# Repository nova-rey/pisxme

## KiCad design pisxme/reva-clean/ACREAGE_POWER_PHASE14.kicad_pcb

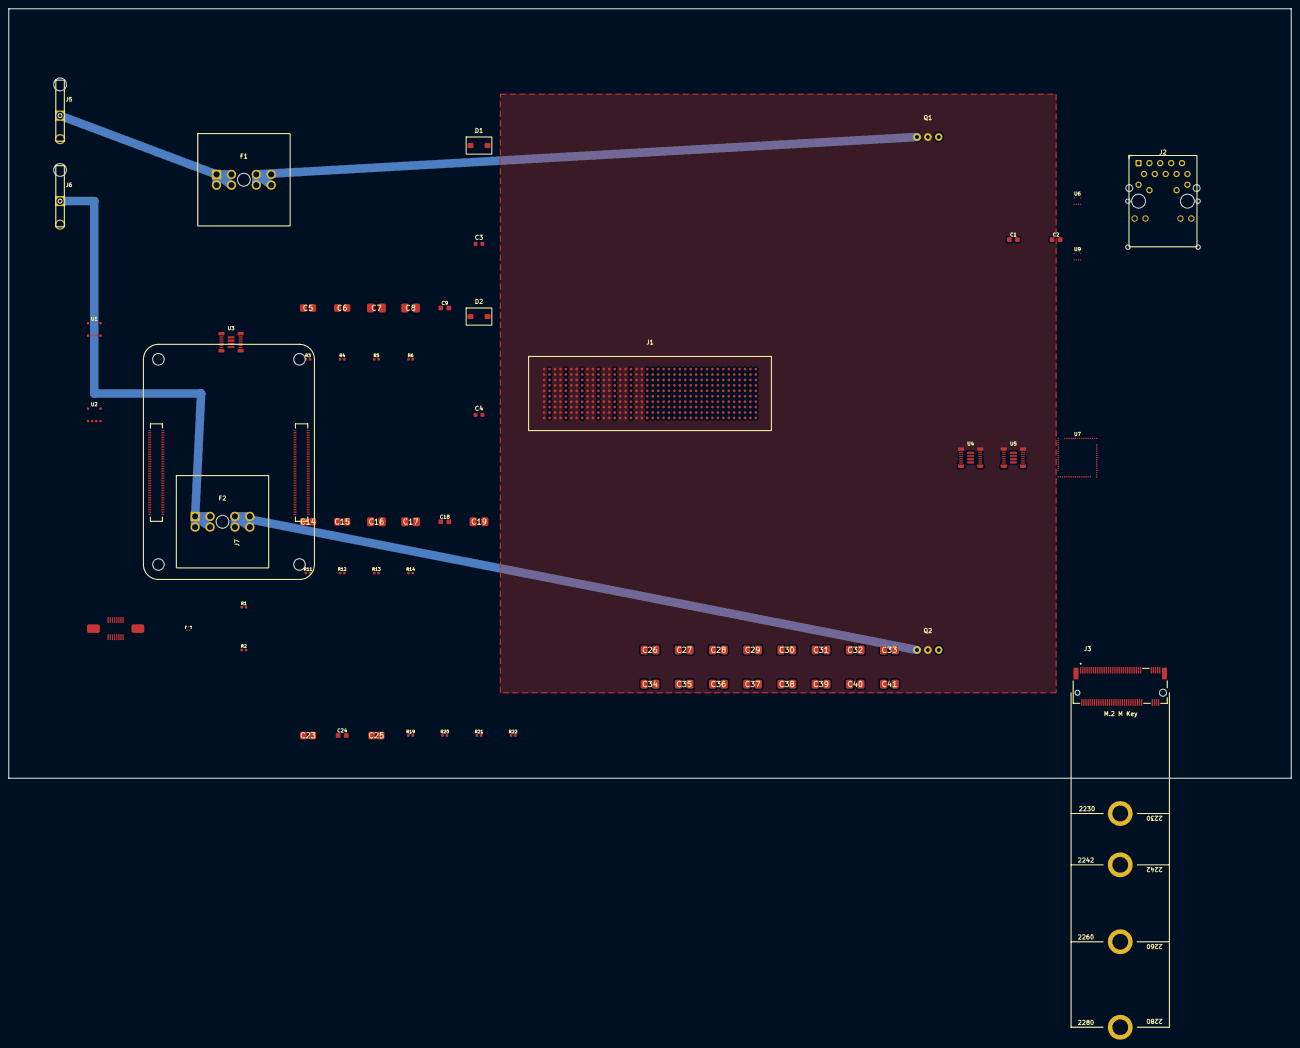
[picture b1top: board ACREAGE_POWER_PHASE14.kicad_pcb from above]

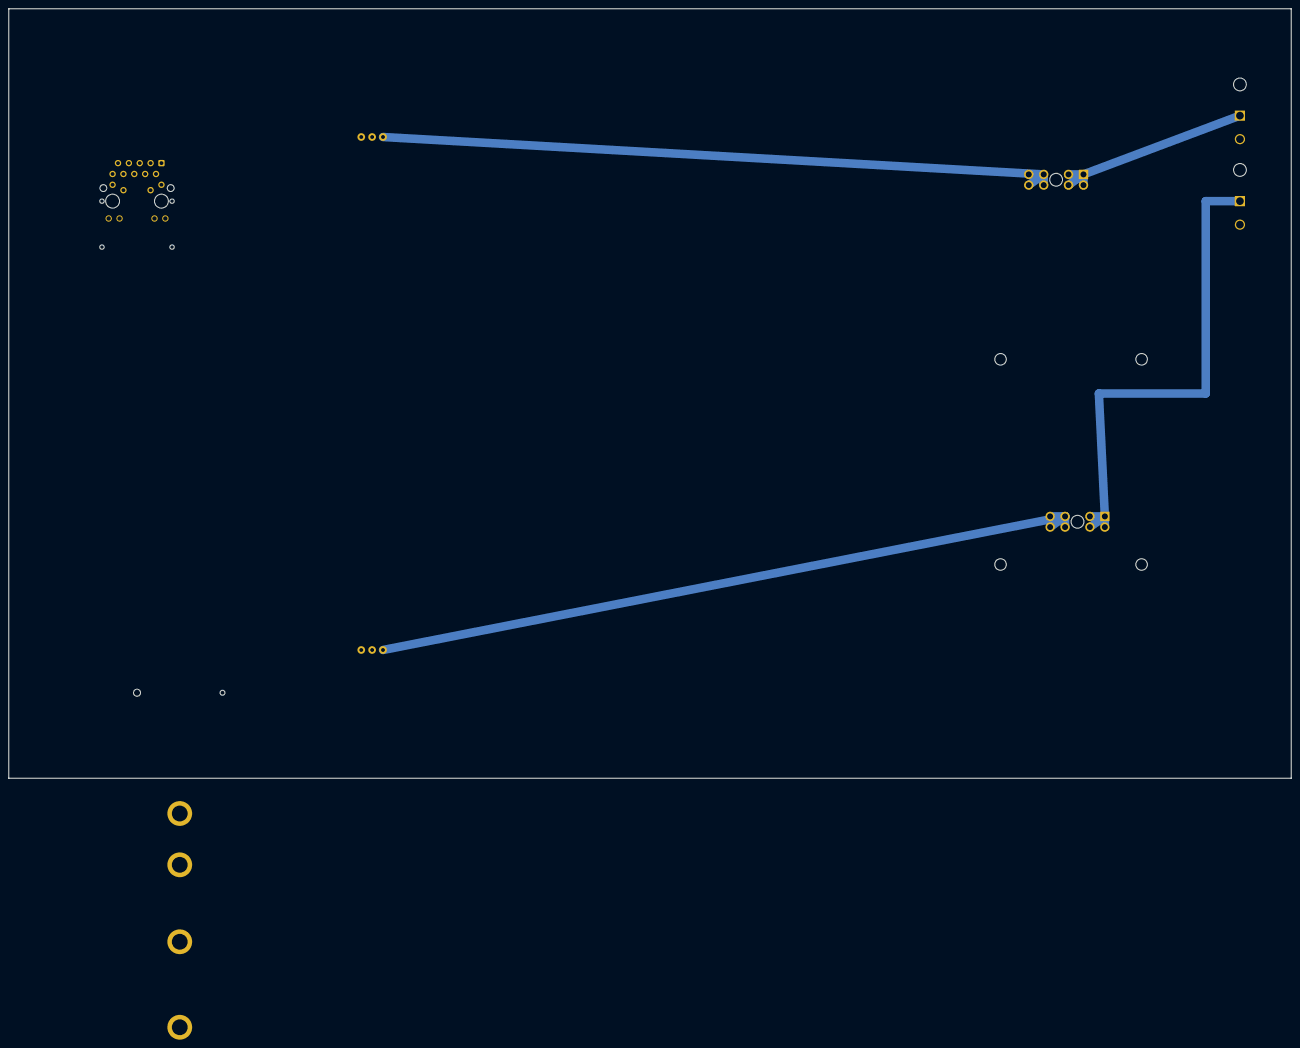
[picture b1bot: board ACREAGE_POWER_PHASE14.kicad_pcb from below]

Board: 6 copper layers, 300.0 x 180.0 mm, 72 parts (2 on the bottom side), 48 nets.

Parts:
C1, C2, C9, C18, C24: C_0805_2012Metric
C3, C4: C_0603_1608Metric
C5, C6, C14, C15, C23, C25: C_1206_3216Metric
C7, C8, C16, C17, C19, C26, C27, C28, C29, C30, C31, C32, C33, C34, C35, C36, C37, C38, C39, C40, C41: C_1210_3225Metric
D1, D2: SMBJ18A; TVS_SMBJ18A_DO214AA
F1, F2: 178.6165.0001; ATO_FuseHolder_17861650001
J1: 74221-101LF; PiSXMeRevAClean_SXM2_74221_101LF
J2: A70-112-331N126; EDAC_A70_112_331N126
J3: JAE SM3ZS067U410ABR1000 B-key SATA socket; JAE_SM3ZS067U410ABR1000_BKEY
J4: Amphenol 10171746-00021LF USB-C USB2 SERVICE; USB_C_SERVICE_10171746
J5, J6: 0039300020; Molex_0039300020_5569_2P_RA
J7: Raspberry-Pi-5-Compute-Module; PiSXMeRevAClean_Raspberry_Pi_5_Compute_Module
MECH_M2_2280: JAE SM3ZS067U410ABR1000 / 2280 card envelope; M2_2280_RETENTION_ENVELOPE
MECH_V100: REV_A_EMPIRICAL_RISK: 150x95mm cooler/backplate e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; V100_COOLER_BACKPLATE_ENVELOPE
Q1, Q2: CSD19536KCS; CSD19536KCS_TO220
R1, R2, R3, R4, R5, R6, R11, R12, R13, R14, R19, R20, R21, R22: R_0402_1005Metric
U1, U2: LM74700QDBVRQ1; LM74700QDBVRQ1_SOT23_6
U3, U4, U5: TPSM63606RDLR; TPSM63606RDLR_RDL0020
U6, U9: TPD4E004DRYR; TPD4E004DRYR_WSON6
U7: TUSB9261IPVP; TUSB9261IPVP_HTQFP64
U8: Texas_DRT_3

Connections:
12V_PROTECTED: C5.1, C6.1, C14.1, C15.1, C23.1, C24.1, C25.1, J1.A22, J1.A23, J1.A25, J1.A26, J1.A28, J1.A29, J1.A31, J1.A32, J1.A34, J1.A35, J1.A37, J1.A38, J1.A40, J1.B22, J1.B23, J1.B25, J1.B26, J1.B28, J1.B29, J1.B31, J1.B32, J1.B34, J1.B35, J1.B37, J1.B38, J1.B40, J1.C22, J1.C23, J1.C25, J1.C26, J1.C28, J1.C29, J1.C31, J1.C32, J1.C34, J1.C35, J1.C37, J1.C38, J1.C40, J1.D22, J1.D23, J1.D25, J1.D26, J1.D28, J1.D29, J1.D31, J1.D32, J1.D34, J1.D35, J1.D37, J1.D38, J1.D40, J1.E22, J1.E23, J1.E25, J1.E26, J1.E28, J1.E29, J1.E31, J1.E32, J1.E34, J1.E35, J1.E37, J1.E38, J1.E40, J1.F22, J1.F23, J1.F25, J1.F26, J1.F28, J1.F29, J1.F31, J1.F32, J1.F34, J1.F35, J1.F37, J1.F38, J1.F40, J1.G22, J1.G23, J1.G25, J1.G26, J1.G28, J1.G29, J1.G31, J1.G32, J1.G34, J1.G35, J1.G37, J1.G38, J1.G40, J1.H22, J1.H23, J1.H25, J1.H26, J1.H28, J1.H29, J1.H31, J1.H32, J1.H34, J1.H35, J1.H37, J1.H38, J1.H40, J1.J22, J1.J23, J1.J25, J1.J26, J1.J28, J1.J29, J1.J31, J1.J32, J1.J34, J1.J35, J1.J37, J1.J38, J1.J40, J1.K22, J1.K23, J1.K25, J1.K26, J1.K28, J1.K29, J1.K31, J1.K32, J1.K34, J1.K35, J1.K37, J1.K38, J1.K40, Q1.2, Q2.2, U1.4, U2.4, U3.1, U3.5, U3.14, U3.16, U4.1, U4.5, U4.14, U4.16, U5.1, U5.5, U5.14, U5.16
/CORE_CM5/CM5_5V: J7.77, J7.79, J7.81, J7.83, J7.85, J7.87
/CORE_CM5/CM5_PER0_N: J1.A3, J7.118
/CORE_CM5/CM5_PER0_P: J1.A2, J7.116
/CORE_CM5/CM5_PERST: J1.E18, J7.109
/CORE_CM5/CM5_PET0_N: C2.1, J7.124
/CORE_CM5/CM5_PET0_P: C1.1, J7.122
/CORE_CM5/CM5_REFCLK_N: J1.F7, J7.112
/CORE_CM5/CM5_REFCLK_P: J1.E7, J7.110
/CORE_CM5/POWER_GND: J7.1, J7.2, J7.7, J7.8, J7.13, J7.14, J7.22, J7.23, J7.32, J7.33, J7.42, J7.43, J7.52, J7.53, J7.59, J7.60, J7.65, J7.66, J7.71, J7.74, J7.98, J7.107, J7.108, J7.113, J7.114, J7.119, J7.120, J7.125, J7.126, J7.131, J7.132, J7.137, J7.138, J7.144, J7.150, J7.155, J7.156, J7.161, J7.162, J7.167, J7.168, J7.173, J7.174, J7.179, J7.180, J7.185, J7.186, J7.191, J7.192, J7.197, J7.198
/ETHERNET/ETH_GND: U6.6, U9.6
/ETHERNET/ETH_POWER: U6.5, U9.5
/ETHERNET/GBE_SHIELD: J2.1, J2.2
/POWER_INPUT/12V_IN_A: C3.2, F1.1, F1.2, F1.3, F1.4, J5.1, U1.3
/POWER_INPUT/12V_IN_B: C4.2, F2.1, F2.2, F2.3, F2.4, J6.1, U2.3
/POWER_INPUT/FUSED_12V_A: D1.1, F1.5, F1.6, F1.7, F1.8, Q1.1, U1.6
/POWER_INPUT/FUSED_12V_B: D2.1, F2.5, F2.6, F2.7, F2.8, Q2.1, U2.6
/POWER_INPUT/GATE_A: Q1.3, U1.5
/POWER_INPUT/GATE_B: Q2.3, U2.5
/POWER_INPUT/VCAP_A: C3.1, U1.1
/POWER_INPUT/VCAP_B: C4.1, U2.1
/REGULATORS/BRIDGE_1V1: C26.1, C27.1, C28.1, C29.1, C30.1, C31.1, C32.1, C33.1, C34.1, C35.1, C36.1, C37.1, C38.1, C39.1, C40.1, C41.1, R19.1, R22.1, U5.8, U5.9
/REGULATORS/BRIDGE_3V3: C16.1, C17.1, C18.2, C19.1, R11.1, R14.1, U4.8, U4.9
/REGULATORS/CM5_5V: C7.1, C8.1, C9.2, R3.1, R6.1, U3.8, U3.9
/REGULATORS/FB_BRIDGE_1V1: R19.2, R20.1, U5.10
/REGULATORS/FB_BRIDGE_3V3: C18.1, R11.2, R12.1, U4.10
/REGULATORS/FB_CM5_5V: C9.1, R3.2, R4.1, U3.10
/REGULATORS/NC: U3.15, U4.15, U5.15
/REGULATORS/PG_BRIDGE_1V1: R22.2, U5.13
/REGULATORS/PG_BRIDGE_3V3: R14.2, U4.13
/REGULATORS/PG_CM5_5V: R6.2, U3.13
/REGULATORS/RT_BRIDGE_1V1: R21.1, U5.12
/REGULATORS/RT_BRIDGE_3V3: R13.1, U4.12
/REGULATORS/RT_CM5_5V: R5.1, U3.12
/SERVICE/SERVICE_GND: J4.A1, J4.A4, J4.A5, J4.A6, J4.A7, J4.A9, J4.A12, J4.B1, J4.B4, J4.B5, J4.B6, J4.B7, J4.B9, J4.B12, R1.1, R1.2, R2.1, R2.2, U8.1, U8.2, U8.3
/STORAGE/BRIDGE_3V3: J3.1, U7.4
/STORAGE/BRIDGE_SATA_RX_N: J3.2, J3.3, J3.4, J3.5, J3.6, U7.5, U7.6, U7.7, U7.8, U7.9
/V100_PCIE/V100_PET0_N: C2.2, J1.G2
/V100_PCIE/V100_PET0_P: C1.2, J1.G1
CM5_GBE_TD0_N: J2.17, J7.10, U6.2
CM5_GBE_TD0_P: J2.18, J7.12, U6.1
CM5_GBE_TD1_N: J2.15, J7.6, U6.4
CM5_GBE_TD1_P: J2.16, J7.4, U6.3
CM5_GBE_TD2_N: J2.13, J7.9, U9.2
CM5_GBE_TD2_P: J2.14, J7.11, U9.1
CM5_GBE_TD3_N: J2.11, J7.5, U9.4
CM5_GBE_TD3_P: J2.12, J7.3, U9.3
POWER_GND: C5.2, C6.2, C7.2, C8.2, C14.2, C15.2, C16.2, C17.2, C19.2, C23.2, C24.2, C25.2, C26.2, C27.2, C28.2, C29.2, C30.2, C31.2, C32.2, C33.2, C34.2, C35.2, C36.2, C37.2, C38.2, C39.2, C40.2, C41.2, D1.2, D2.2, J1.A21, J1.A24, J1.A27, J1.A30, J1.A33, J1.A36, J1.A39, J1.B21, J1.B24, J1.B27, J1.B30, J1.B33, J1.B36, J1.B39, J1.C21, J1.C24, J1.C27, J1.C30, J1.C33, J1.C36, J1.C39, J1.D21, J1.D24, J1.D27, J1.D30, J1.D33, J1.D36, J1.D39, J1.E21, J1.E24, J1.E27, J1.E30, J1.E33, J1.E36, J1.E39, J1.F21, J1.F24, J1.F27, J1.F30, J1.F33, J1.F36, J1.F39, J1.G21, J1.G24, J1.G27, J1.G30, J1.G33, J1.G36, J1.G39, J1.H21, J1.H24, J1.H27, J1.H30, J1.H33, J1.H36, J1.H39, J1.J21, J1.J24, J1.J27, J1.J30, J1.J33, J1.J36, J1.J39, J1.K21, J1.K24, J1.K27, J1.K30, J1.K33, J1.K36, J1.K39, J5.2, J6.2, R4.2, R5.2, R12.2, R13.2, R20.2, R21.2, U1.2, U2.2, U3.6, U3.11, U3.17, U3.18, U3.19, U3.20, U4.6, U4.11, U4.17, U4.18, U4.19, U4.20, U5.6, U5.11, U5.17, U5.18, U5.19, U5.20

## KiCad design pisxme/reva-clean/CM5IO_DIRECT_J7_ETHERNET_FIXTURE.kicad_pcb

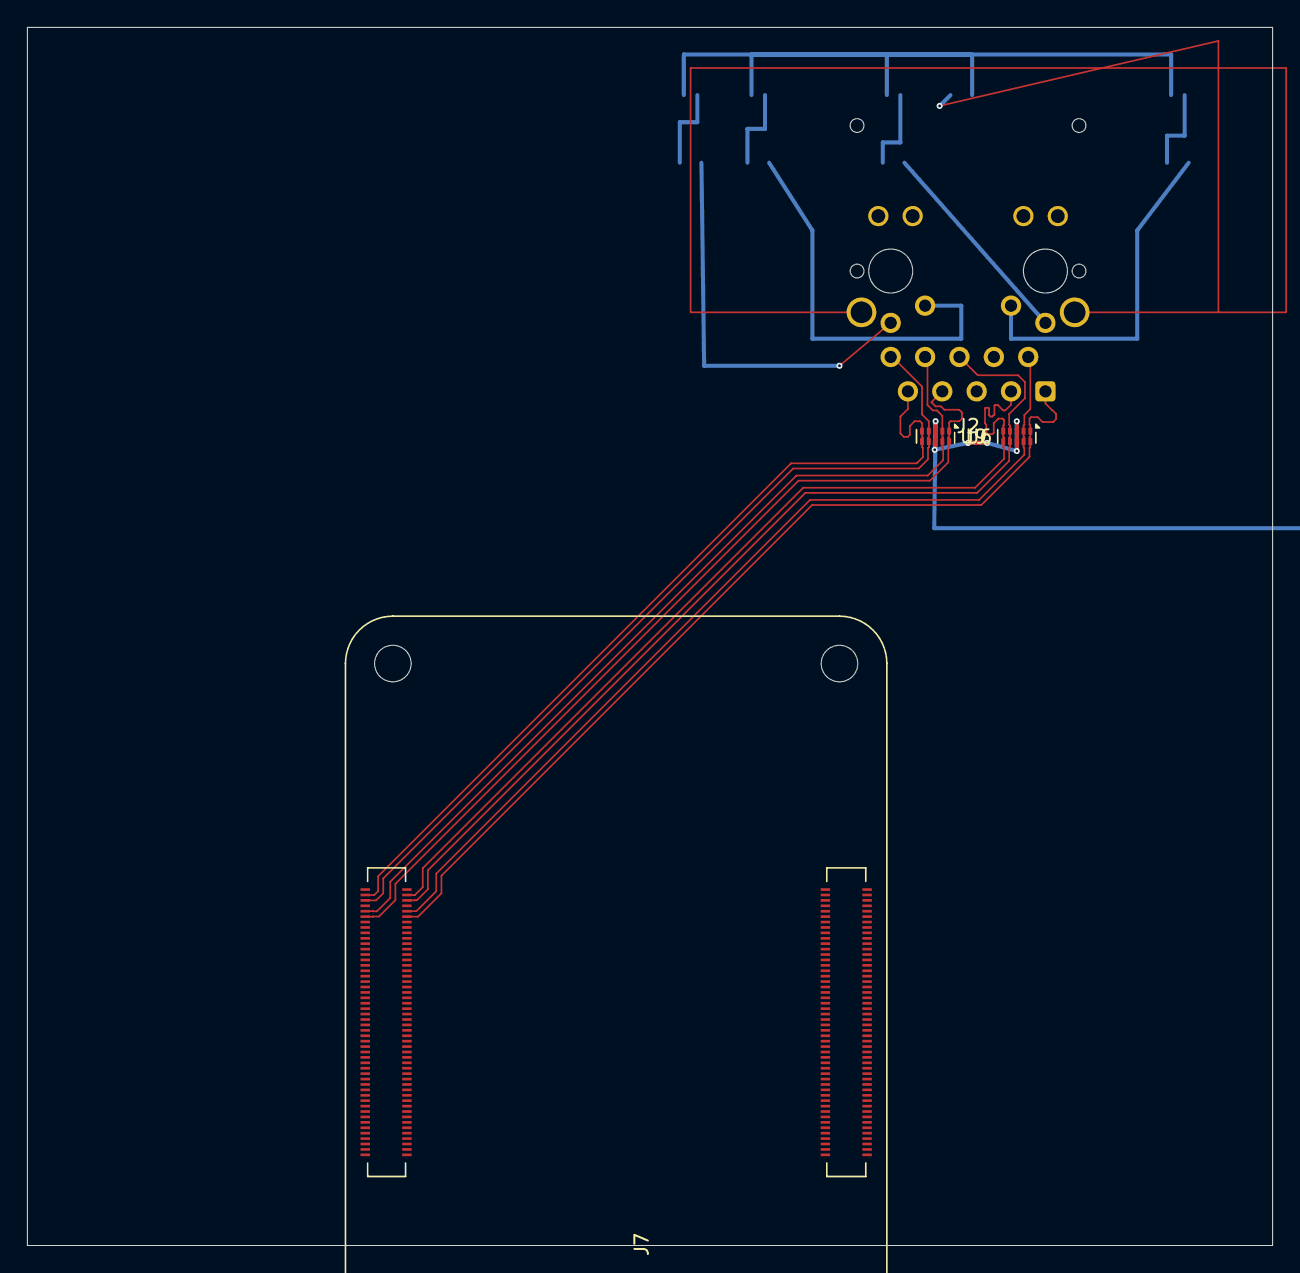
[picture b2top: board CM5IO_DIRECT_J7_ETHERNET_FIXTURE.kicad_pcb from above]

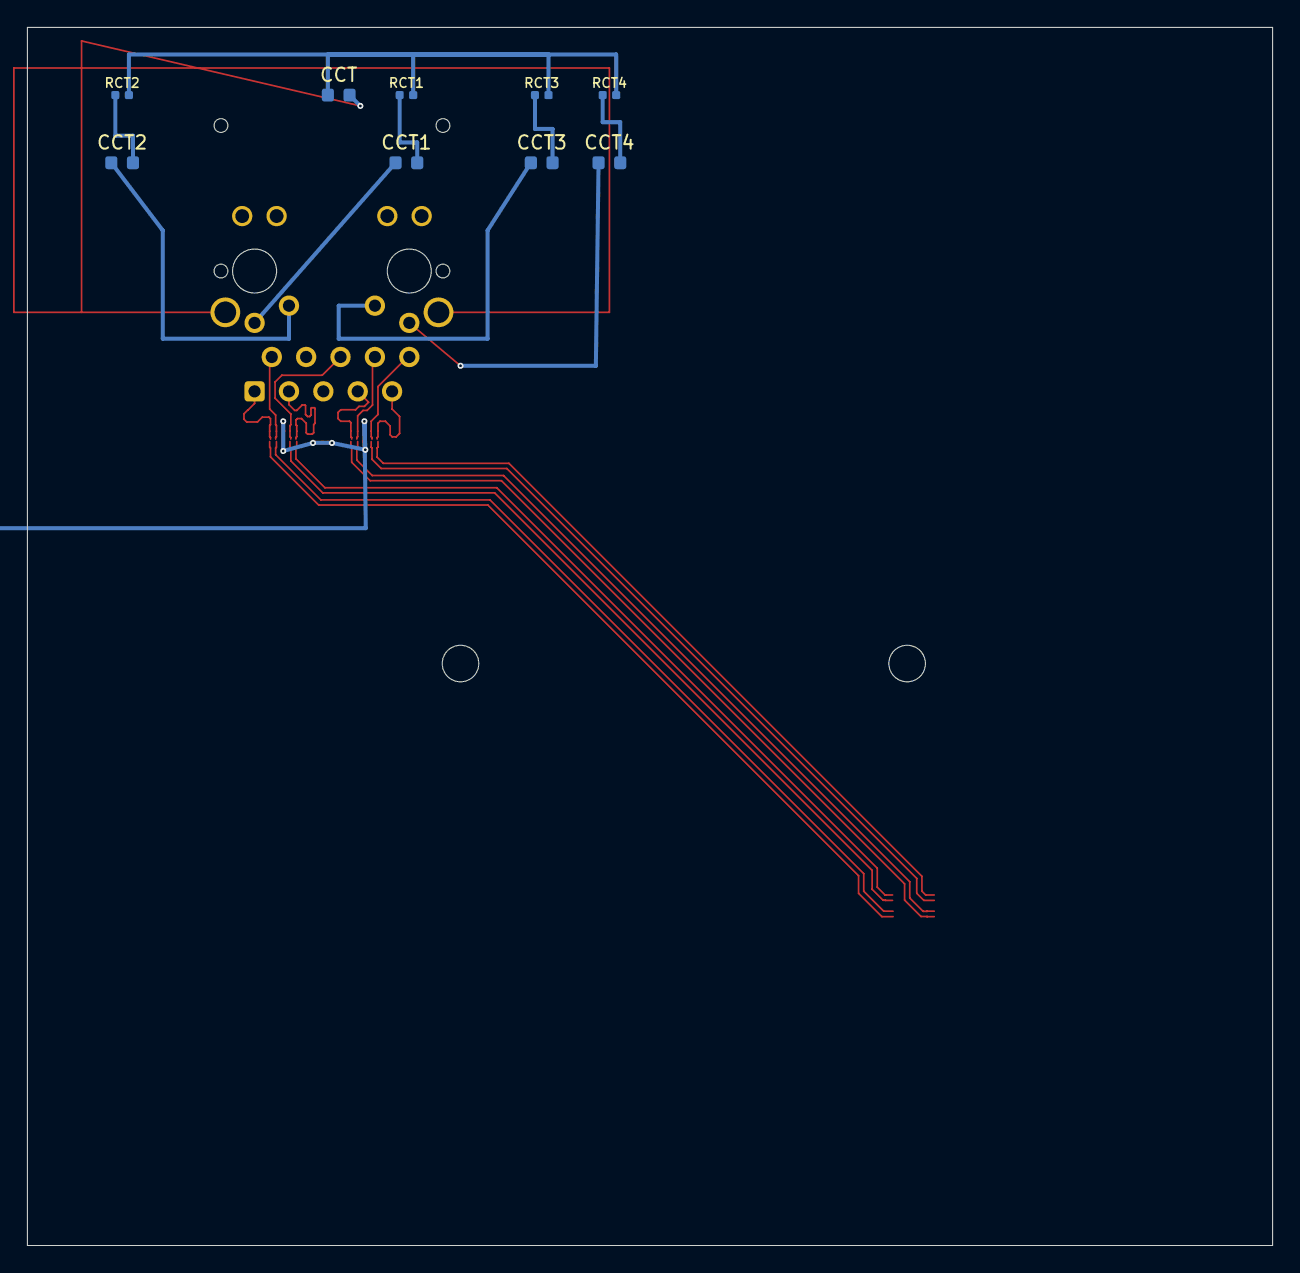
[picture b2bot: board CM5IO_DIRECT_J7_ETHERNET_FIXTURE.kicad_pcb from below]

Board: 6 copper layers, 92.0 x 90.0 mm, 13 parts (9 on the bottom side), 19 nets.

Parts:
CCT, CCT1, CCT2, CCT3, CCT4: C_0603_1608Metric
J2: A70-112-331N126; EDAC_A70_112_331N126
J7: Raspberry-Pi-5-Compute-Module; PiSXMeRevAClean_Raspberry_Pi_5_Compute_Module
RCT1, RCT2, RCT3, RCT4: R_0402_1005Metric
U6, U9: TPD4EUSB30; USON-10_2.5x1.0mm_P0.5mm

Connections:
CM5_GBE_TD0_N: J2.2, J7.10, U6.2 (D1-), U6.9
CM5_GBE_TD0_P: J2.1, J7.12, U6.1 (D1+), U6.10
CM5_GBE_TD1_N: J2.6, J7.6, U6.4 (D2+), U6.7
CM5_GBE_TD1_P: J2.3, J7.4, U6.5 (D2-), U6.6
CM5_GBE_TD2_N: J2.8, J7.9, U9.2 (D1-), U9.9
CM5_GBE_TD2_P: J2.7, J7.11, U9.1 (D1+), U9.10
CM5_GBE_TD3_N: J2.10, J7.5, U9.4 (D2+), U9.7
CM5_GBE_TD3_P: J2.9, J7.3, U9.5 (D2-), U9.6
ETH_CT1: CCT1.1, J2.11
ETH_CT2: CCT2.1, J2.12
ETH_CT3: CCT3.1, J2.13
ETH_CT4: CCT4.1, J2.14
ETH_CT_BRANCH_1: CCT1.2, RCT1.1
ETH_CT_BRANCH_2: CCT2.2, RCT2.1
ETH_CT_BRANCH_3: CCT3.2, RCT3.1
ETH_CT_BRANCH_4: CCT4.2, RCT4.1
ETH_CT_COMMON: CCT.1, RCT1.2, RCT2.2, RCT3.2, RCT4.2
ETH_GND: U6.3 (GND), U6.8 (GND), U9.3 (GND), U9.8 (GND)
GBE_SHIELD: CCT.2, J2.19, J2.20

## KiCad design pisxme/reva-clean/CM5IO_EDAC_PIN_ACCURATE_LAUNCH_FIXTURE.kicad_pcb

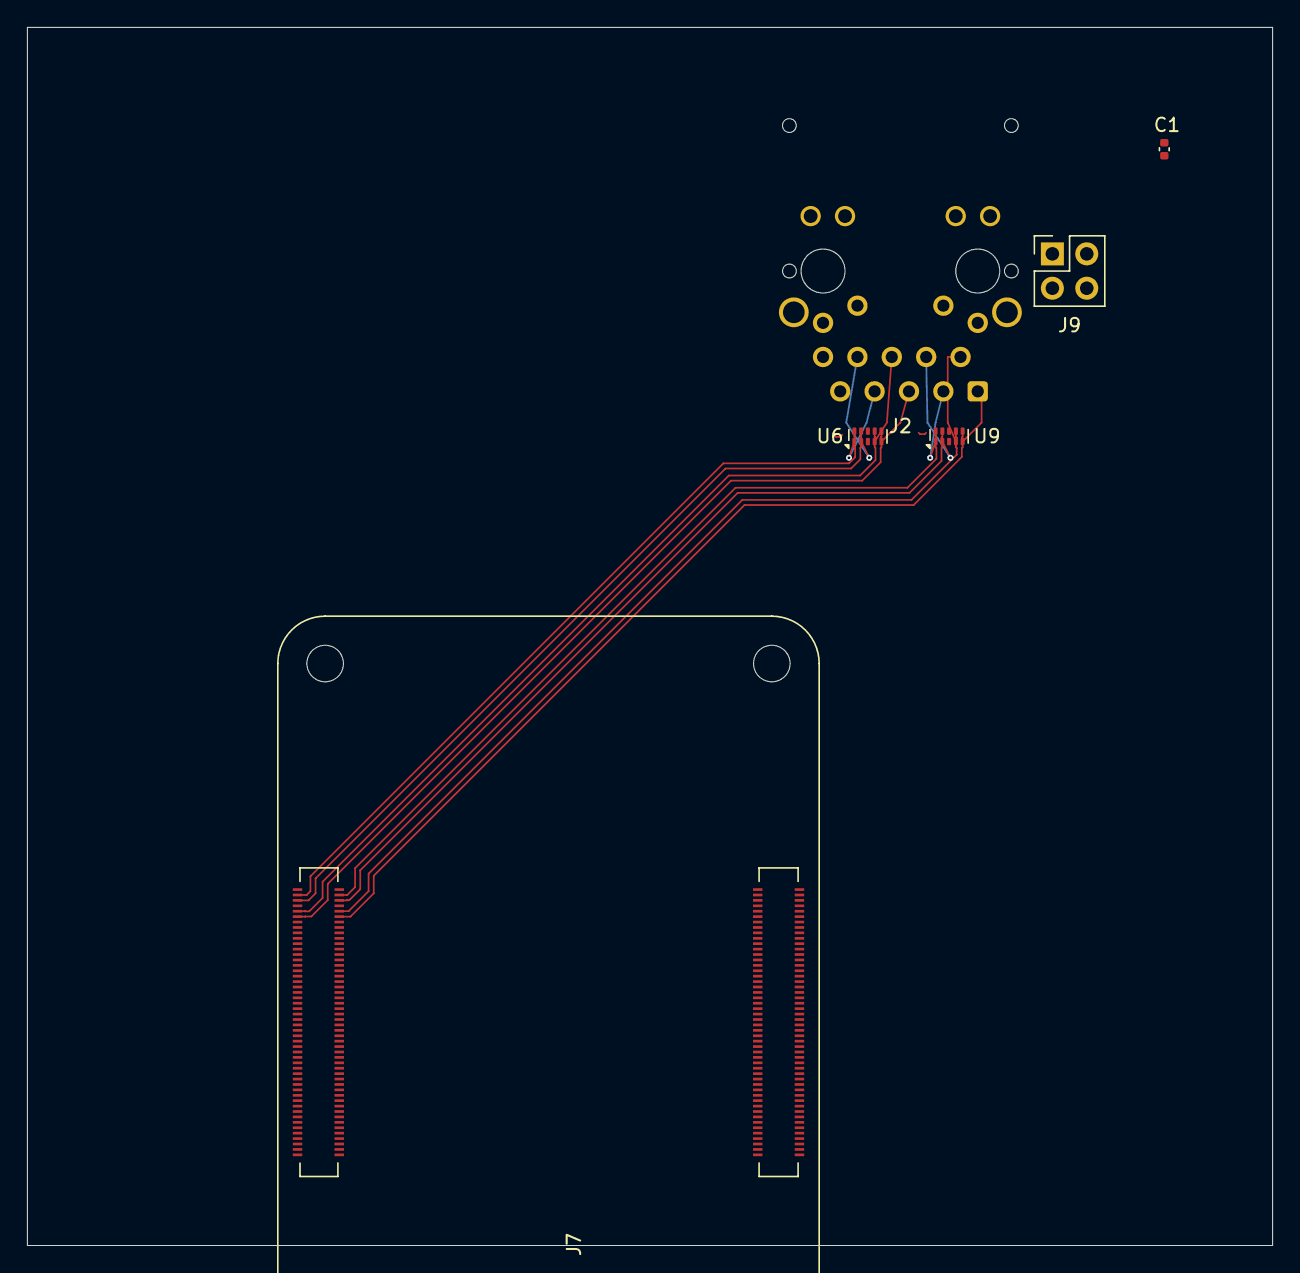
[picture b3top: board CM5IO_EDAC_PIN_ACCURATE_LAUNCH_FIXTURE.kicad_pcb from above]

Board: 6 copper layers, 92.0 x 90.0 mm, 6 parts (0 on the bottom side), 11 nets.

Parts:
C1: 100n; C_0402_1005Metric
J2: A70-112-331N126; EDAC_A70_112_331N126
J7: Raspberry-Pi-5-Compute-Module; PiSXMeRevAClean_Raspberry_Pi_5_Compute_Module
J9: THD-02-R; PinHeader_2x02_P2.54mm_Vertical
U6, U9: TPD4EUSB30; USON-10_2.5x1.0mm_P0.5mm

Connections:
CM5_GBE_TD0_N: J2.2, J7.10, U9.4 (D2+), U9.7
CM5_GBE_TD0_P: J2.1, J7.12, U9.5 (D2-), U9.6
CM5_GBE_TD1_N: J2.4, J7.6, U9.2 (D1-), U9.9
CM5_GBE_TD1_P: J2.3, J7.4, U9.1 (D1+), U9.10
CM5_GBE_TD2_N: J2.6, J7.9, U6.4 (D2+), U6.7
CM5_GBE_TD2_P: J2.5, J7.11, U6.5 (D2-), U6.6
CM5_GBE_TD3_N: J2.8, J2.10, J7.5, U6.2 (D1-), U6.9
CM5_GBE_TD3_P: J2.7, J2.9, J7.3, U6.1 (D1+), U6.10
ETH_CT_COMMON: C1.1, J2.11, J2.12, J2.13, J2.14, J9.1, J9.2, J9.3, J9.4
ETH_GND: C1.2, U6.3 (GND), U6.8 (GND), U9.3 (GND), U9.8 (GND)
GBE_SHIELD: J2.19, J2.20
